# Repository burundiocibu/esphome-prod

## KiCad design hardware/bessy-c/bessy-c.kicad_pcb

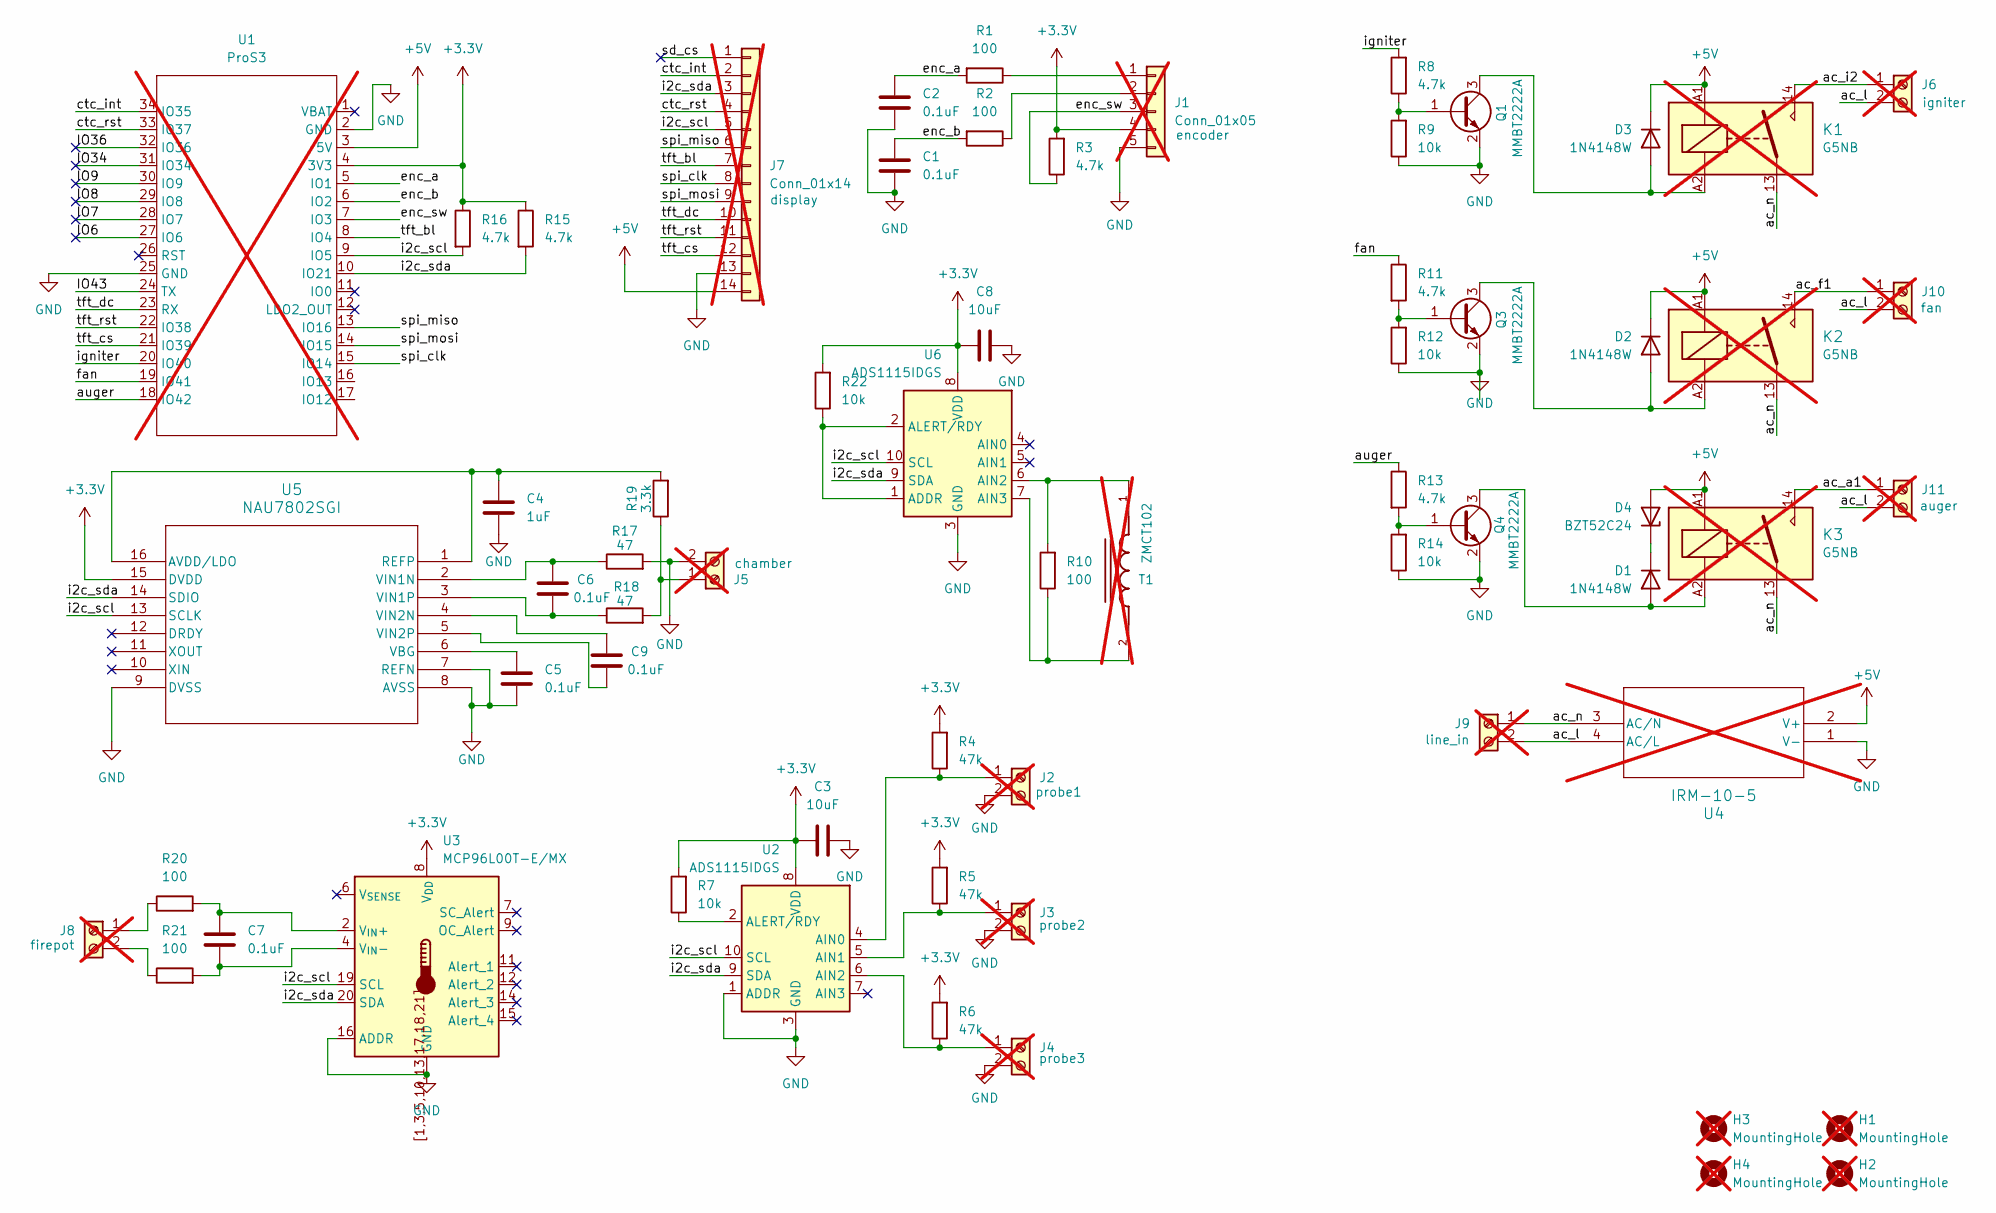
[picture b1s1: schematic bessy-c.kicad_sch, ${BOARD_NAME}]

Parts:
C1, C2, C5, C6, C7, C9: 0.1uF; C_0805_2012Metric
C3, C8: 10uF; C_0805_2012Metric
C4: 1uF; C_0805_2012Metric
D1, D2, D3: 1N4148W; D_SOD-123
D4: BZT52C24; D_SOD-123F
H1, H2, H3, H4: MountingHole; MountingHole_3.2mm_M3; not fitted
J1: Conn_01x05; PinHeader_1x05_P2.54mm_Vertical; not fitted
J2, J3, J4, J5, J6, J8, J9, J10, J11: DB300V-5.0-2P-BK-S; TerminalBlock_MaiXu_MX126-5.0-02P_1x02_P5.00mm; not fitted
J7: Conn_01x14; PinHeader_1x14_P2.54mm_Vertical; not fitted
K1, K2, K3: G5NB; Relay_SPST_Omron_G5NB; not fitted
Q1, Q3, Q4: MMBT2222A; SOT-23
R1, R2, R10, R20, R21: 100; R_0805_2012Metric
R3, R8, R11, R13, R15, R16: 4.7k; R_0805_2012Metric
R4, R5, R6: 47k; R_0805_2012Metric
R7, R9, R12, R14, R22: 10k; R_0805_2012Metric
R17, R18: 47; R_0805_2012Metric
R19: 3.3k; R_0805_2012Metric
T1: ZMCT102; XFMR_ZMCT102; PARTREV N/A; not fitted
U1: ProS3; ProS3_SMD; not fitted
U2, U6: ADS1115IDGS; TSSOP-10_3x3mm_P0.5mm
U3: MCP96L00T-E/MX; QFN-20-1EP_5x5mm_P0.65mm_EP3.35x3.35mm
U4: IRM-10-5; IRM-10_MWU; not fitted
U5: NAU7802SGI; SOI16_NAU7802SGI_NUV

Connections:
+3.3V: C3.1, C8.1, J1.4, R3.2, R4.2, R5.2, R6.2, R7.2, R15.1, R16.1, R22.2, U1.4 (3V3), U2.8 (VDD), U3.8 (V_{DD}), U5.15 (DVDD), U6.8 (VDD)
+5V: D2.1 (K), D3.1 (K), D4.2 (A), J7.14, K1.A1, K2.A1, K3.A1, U1.3 (5V), U4.2 (V+)
/IO6: U1.27 (IO6)
/IO7: U1.28 (IO7)
/IO8: U1.29 (IO8)
/IO9: U1.30 (IO9)
/IO34: U1.31 (IO34)
/IO36: U1.32 (IO36)
/IO43: U1.24 (TX)
/ac_a1: J11.1, K3.14
/ac_f1: J10.1, K2.14
/ac_i2: J6.1, K1.14
/ac_l: J6.2, J9.2, J10.2, J11.2, U4.4 (AC/L)
/ac_n: J9.1, K1.13, K2.13, K3.13, U4.3 (AC/N)
/auger: R13.1, U1.18 (IO42)
/ctc_int: J7.2, U1.34 (IO35)
/ctc_rst: J7.4, U1.33 (IO37)
/enc_a: C2.1, R1.2, U1.5 (IO1)
/enc_b: C1.1, R2.2, U1.6 (IO2)
/enc_sw: J1.3, R3.1, U1.7 (IO3)
/fan: R11.1, U1.19 (IO41)
/i2c_scl: J7.5, R16.2, U1.9 (IO5), U2.10 (SCL), U3.19 (SCL), U5.13 (SCLK), U6.10 (SCL)
/i2c_sda: J7.3, R15.2, U1.10 (IO21), U2.9 (SDA), U3.20 (SDA), U5.14 (SDIO), U6.9 (SDA)
/igniter: R8.2, U1.20 (IO40)
/sd_cs: J7.1
/spi_clk: J7.8, U1.15 (IO14)
/spi_miso: J7.6, U1.13 (IO16)
/spi_mosi: J7.9, U1.14 (IO15)
/tft_bl: J7.7, U1.8 (IO4)
/tft_cs: J7.12, U1.21 (IO39)
/tft_dc: J7.10, U1.23 (RX)
/tft_rst: J7.11, U1.22 (IO38)
GND: C1.2, C2.2, C3.2, C4.1, C5.1, C8.2, J1.5, J2.2, J3.2, J4.2, J5.2, J7.13, Q1.2 (E), Q3.2 (E), Q4.2 (E), R9.1, R12.1, R14.1, R17.2, U1.2 (GND), U1.25 (GND), U2.1 (ADDR), U2.3 (GND), U3.1 (GND), U3.3 (GND), U3.5 (GND), U3.10 (GND), U3.13 (GND), U3.16 (ADDR), U3.17 (GND), U3.18 (GND), U3.21 (GND), U3.[1,3,5,10,13,17,18,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 (GND), U4.1 (V-), U5.7 (REFN), U5.8 (AVSS), U5.9 (DVSS), U6.3 (GND)
unnamed: D1.2 (A), K3.A2, Q4.3 (C)
unnamed: D1.1 (K), D4.1 (K)
unnamed: D2.2 (A), K2.A2, Q3.3 (C)
unnamed: D3.2 (A), K1.A2, Q1.3 (C)
unnamed: J1.1, R1.1
unnamed: J1.2, R2.1
unnamed: J2.1, R4.1, U2.4 (AIN0)
unnamed: J3.1, R5.1, U2.5 (AIN1)
unnamed: J4.1, R6.1, U2.6 (AIN2)
unnamed: J5.1, R18.2, R19.1
unnamed: J8.1, R20.1
unnamed: J8.2, R21.1
unnamed: Q1.1 (B), R8.1, R9.2
unnamed: Q3.1 (B), R11.2, R12.2
unnamed: Q4.1 (B), R13.2, R14.2
unnamed: R7.1, U2.2 (ALERT/RDY)
unnamed: C7.2, R20.2, U3.2 (V_{IN}+)
unnamed: C7.1, R21.2, U3.4 (V_{IN}-)
unnamed: C4.2, R19.2, U5.1 (REFP), U5.16 (AVDD/LDO)
unnamed: C5.2, U5.6 (VBG)
unnamed: C6.2, R17.1, U5.2 (VIN1N)
unnamed: C6.1, R18.1, U5.3 (VIN1P)
unnamed: C9.2, U5.4 (VIN2N)
unnamed: C9.1, U5.5 (VIN2P)
unnamed: R22.1, U6.1 (ADDR), U6.2 (ALERT/RDY)
unnamed: R10.2, T1.1, U6.6 (AIN2)
unnamed: R10.1, T1.2, U6.7 (AIN3)

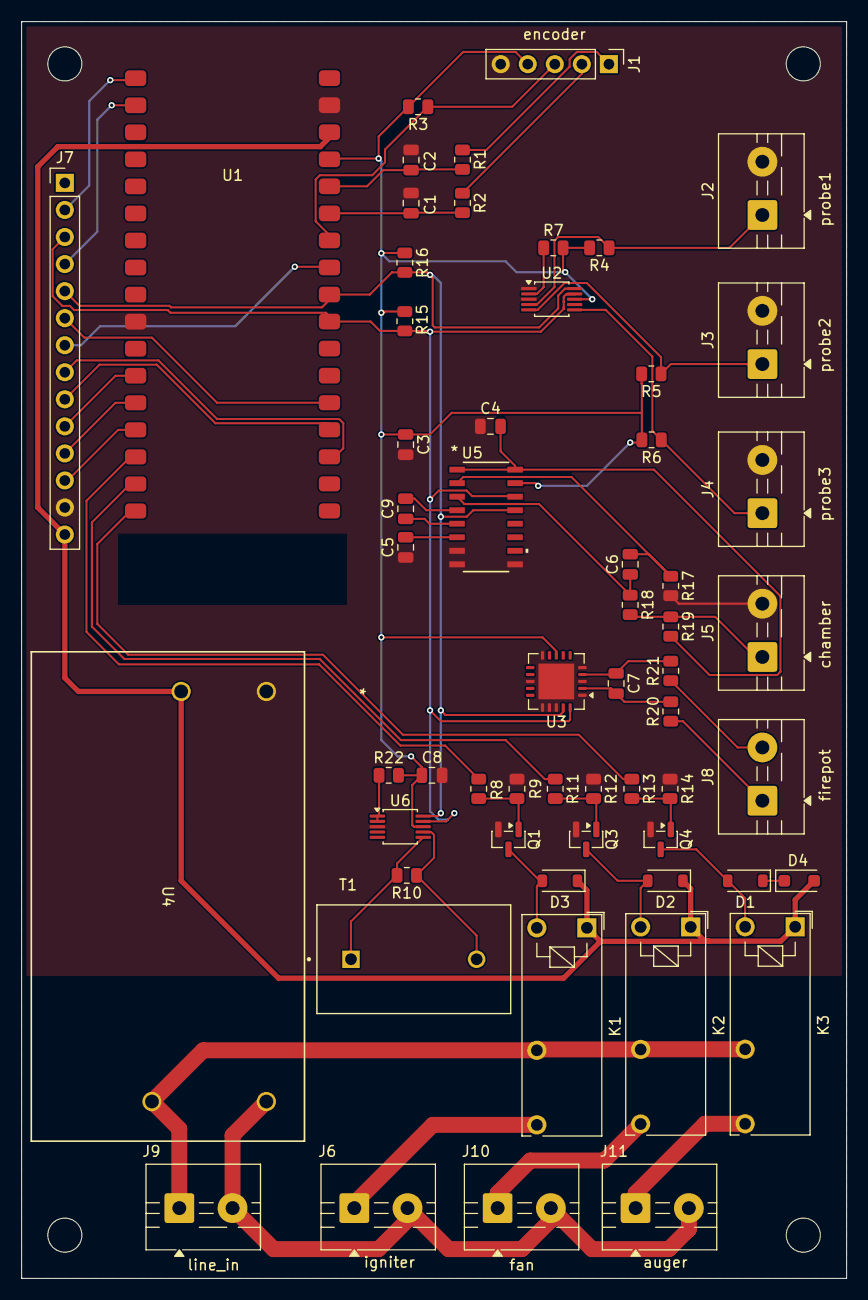
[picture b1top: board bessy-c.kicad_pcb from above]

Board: 2 copper layers, 77.5 x 118.0 mm, 63 parts (0 on the bottom side), 52 nets.

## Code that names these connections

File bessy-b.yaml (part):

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  fan_cooldown_interval_s: "60"  # seconds between sc_shutdown re-checks

  # I/O assignments.
  pin_spi_clk:  GPIO18  # Yellow, row 7
  pin_spi_miso: GPIO19  # Green,  row 8
  pin_spi_mosi: GPIO27  # Blue,   row 9
  pin_tft_cs:   GPIO4   # Grey,   row 10
  pin_tft_dc:   GPIO14  # Violet, row 11
  pin_tft_rst:  GPIO13  # Brown,  row 12
  pin_tft_bl:   GPIO5   # White,  row 13
  pin_rtd_cs:   GPIO16  # Orange, row 14, unused
  pin_i2c_sda:  GPIO21  # Blue,   row 1  , w 4.7k pullup
  pin_i2c_scl:  GPIO22  # Green,  row 17 , w 4.7k pullup
  pin_analog:   GPIO34  # White,  row 18
  pin_enc_a:    GPIO35  # Grey,   row 19 
  pin_enc_b:    GPIO39  # Brown,  row 20
  pin_enc_sw:   GPIO36  # Yellow, row 21, w 10k pullup
  pin_ctc_int:  GPIO23  # White,  row 25, ""
  pin_ctc_rst:  GPIO12  # Violet, row 26, ""
  pin_status:   GPIO23  # White,  row 25
  pin_relay1:   GPIO32  # Auger
  pin_relay2:   GPIO33  # Fan
  pin_relay3:   GPIO25  # Igniter
  pin_relay4:   GPIO26  # Unused

esphome:
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
# ===================== Buses =====================
spi:
  clk_pin: ${pin_spi_clk}
  miso_pin: ${pin_spi_miso}
  mosi_pin: ${pin_spi_mosi}

i2c:
  sda: ${pin_i2c_sda}
  scl: ${pin_i2c_scl}
  scan: true
  frequency: 10kHz # the MCP9600 likes it _slow_

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output:
  - platform: ledc
    pin:
      number: ${pin_tft_bl}
      ignore_strapping_warning: true
    id: tft_backlight

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    id: my_display
    model: ST7796
    rotation: 270
    cs_pin: ${pin_tft_cs}
    dc_pin: ${pin_tft_dc}
    reset_pin: ${pin_tft_rst}
    update_interval: 1s
    invert_colors: true
    color_depth: 8BIT
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    restore_mode: ALWAYS_ZERO
    publish_initial_value: true
    pin_a:
      number: ${pin_enc_a}
      mode:
        input: true
    pin_b:
      number: ${pin_enc_b}
      mode:
        input: true
    on_clockwise:
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    name: "Encoder Button"
    id: encoder_button
    pin:
      number: ${pin_enc_sw}
      mode:
        input: true
      inverted: true
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          condition:
            lambda: return !isnan(id(pot_temp).state) && (id(pot_temp).state * 1.8f + 32.0f) > ${fan_cooldown_temp_f};
          then:
            - logger.log: "Fire pot is still hot, keeping fan on"
            - switch.turn_on: fan
            - script.execute: sc_shutdown
          else:
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              float temp_f = id(pot_temp).state * 1.8f + 32.0f;   // pot_temp is in C
              return !isnan(temp_f) && temp_f > ${fan_cooldown_temp_f};
          then:
            - logger.log: "Fire pot is still hot, keeping fan on"
            - switch.turn_on: fan
            - script.execute: sc_shutdown
          else:
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
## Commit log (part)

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2023-07-12 hehe
2023-09-04 esphome cleanup
2023-10-08 New water meter using a hall-effect sensor
2023-10-08 New water meter
2023-10-09 added board temp to water-meter
2023-10-24 changing envoy-logger to use token auth
2023-12-24 driveway flood
2023-12-26 big cleanup of files
2023-12-26 cleaning up the poe ble devices
2024-01-07 partial cleanup but everyone is working w HA
2024-01-11 unifiying config and enforcing encryption
2024-01-11 using one var for ssid/pw
2024-01-12 forgot temp in porch-3
2024-01-12 forgot the encryption on two
2024-01-14 Fixing heat tape automations
2024-01-14 encrypting the spare
2024-01-29 first cut at garden-water node
2024-02-11 fixed ota pw on 2, biltong scale compiling
2024-03-31 esphome update
2024-04-17 new olla controller and device cleanup
2024-05-05 printer-lights
2024-05-05 updated prom targets
2024-05-18 biltong scale has cal and tare
2024-05-18 adding printer lights
2024-05-27 replacing failed sensors
2024-05-27 replaced sensors
2024-06-21 moving master bath automation to ha
2024-06-23 keeping ha from fussing about units
2024-07-04 fixing new syntax for ota password
2024-08-02 undeleting water meter
2024-10-17 new version of esphome
2024-10-27 refresh
2024-10-28 driveway-ir
2024-11-24 switched tank temp sensors
2025-01-11 update, more cal on tank-level2
2025-01-12 removed old tank level
2025-01-30 added cal point
2025-02-11 more water level cal data
2025-02-14 added a persistant total for water
2025-02-23 Adding cal to tank-level
2025-03-03 fixed water meter totalizer
2025-03-08 first cut at aqi sensor
2025-03-09 removed mqtt from water-meter
2025-04-07 periodic update
2025-05-11 new aqi sensor
2025-05-27 prep to split off esphome
2025-06-27 start of pool level sensor
2025-06-29 Kinda working w MQTT
2025-06-29 Deleted biltong-scale
2025-06-30 now with largely working sleep
2025-07-01 Now accepts a cmd/set sleep_duration
2025-07-01 bringing spare switch into the fold
2025-07-01 fixing ssid
2025-07-01 Removing spare-swithc
2025-07-01 Have a working deep sleep config
2025-07-03 now sending the ToF sensor to sleep
2025-07-05 working pool-level, added text sensor to main-panel
2025-07-10 Deployed pool-level; its still not consistent
2025-07-13 playing with a esp32c6
2025-07-19 Working api based deep sleep in esp32c6
2025-07-20 Working API based deep sleep interface
2025-07-20 esp32c6 update
2025-07-23 adding porch-olla
2025-07-25 Working as well as mqtt can?
2025-07-27 removed test pool level
2025-07-29 Working mqtt + get sleep command from remote
2025-08-15 getting rid of test device
2025-08-17 working mqtt deep sleep config; uses mqtt-responder
2025-08-19 first cut at a current monitor for the bench
2025-08-25 now uses ina228 and is on an adafruit feather
2025-08-25 Now using ab APB2 sensor
2025-08-26 now plots data on display
2025-08-29 Now uses a NAU7802 to sample a throw in pressure sensor
2025-09-07 now deployed w/o deep sleeping
2025-09-13 Now uses an ABP2 pressure sensor. Much better
2025-09-13 Don't recall
2025-09-13 A working mqtt sleep example
2025-09-14 median > average for outiler removal...
2025-09-15 Replaced pool-level w ABP2 based esp32c6
2025-11-05 by bye pearl charger
2025-11-13 out with the old, in with the new
2025-12-13 added oak-radar
2026-01-11 putting the christmas tree away
2026-02-01 re-using the old pearl-charger switch
2026-02-07 disabling oak radar
2026-03-07 replacing the downstairs ac monitor
2026-03-08 finishing up ac-monitor1
2026-03-08 adding a thread esp32-h2 device
2026-03-09 cleaning up current-logger, bringing thread1 back to fully connected
2026-03-31 playing
2026-04-27 thread test
2026-04-27 Now with nau7802 sensor and ds18b20
2026-04-27 switching the nau on and off
2026-04-27 added sleeping to nau7802
2026-04-27 added temperature sensing to the nau
2026-05-03 Now talking to the nau7802 over a longer buss
2026-05-06 calibrated the nau
2026-05-06 starting the actual pool level
2026-05-06 helper cleanup
2026-05-06 cleaning up pool level
2026-05-08 working on tc-cal
2026-05-08 calibrated pool level
2026-05-08 using prometheus for cal data
2026-05-09 prom-cal
2026-05-11 first two stage calibration
2026-05-12 prom-cal: simplify to two-zone calibration only
    Remove single-region fit and residuals modes; --zero-span and
    --cal100-span are now required. Drops tare/cal100/depth_mm metrics.
2026-05-16 post second cal session
2026-05-17 turning thread1 into an FTD
2026-05-17 removing cruft
2026-05-17 replacing device of thread1
2026-05-17 adding a thread rssi sensor
2026-05-18 final cal. hopefully
2026-05-18 its c not python
2026-05-21 increasing data dot size
2026-05-22 removing ble-gw0
2026-05-22 moving aqi-outdoor to thread
2026-05-25 script to capture cal times
2026-06-03 Edit aqi-outdoor.yaml
2026-06-03 Edit pool-level.yaml
2026-06-05 Edit aqi-upstairs.yaml
2026-06-06 Edit tr1.yaml
2026-06-21 fixign openthread ref
2026-06-23 Edit bessy-b.yaml
2026-06-26 bessy-b documentation
2026-06-27 bessy-b: add full hardware config with display, sensors, relays
    - Add complete pin substitutions map
    - Switch display from ili9xxx to mipi_spi (ST7796)
    - Add SPI bus, I2C, ADS1115, MAX31865, MAX31855, ADC, rotary encoder
    - Optimise display lambda to clear per-line rectangles instead of full fill
    - Remove status_led (GPIO23 reserved but unused)
    - Hardware SPI for display; MAX31865 hardware SPI issue noted for later
2026-06-27 added pinout diagram for esp relay 4
2026-06-27 Edit pantry-light.yaml
2026-06-28 display now showing colors as expected
